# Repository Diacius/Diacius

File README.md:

# Hiya :wave:

I'm a human who occasionally writes code, some of it ends up here.

My pronouns are: he/him

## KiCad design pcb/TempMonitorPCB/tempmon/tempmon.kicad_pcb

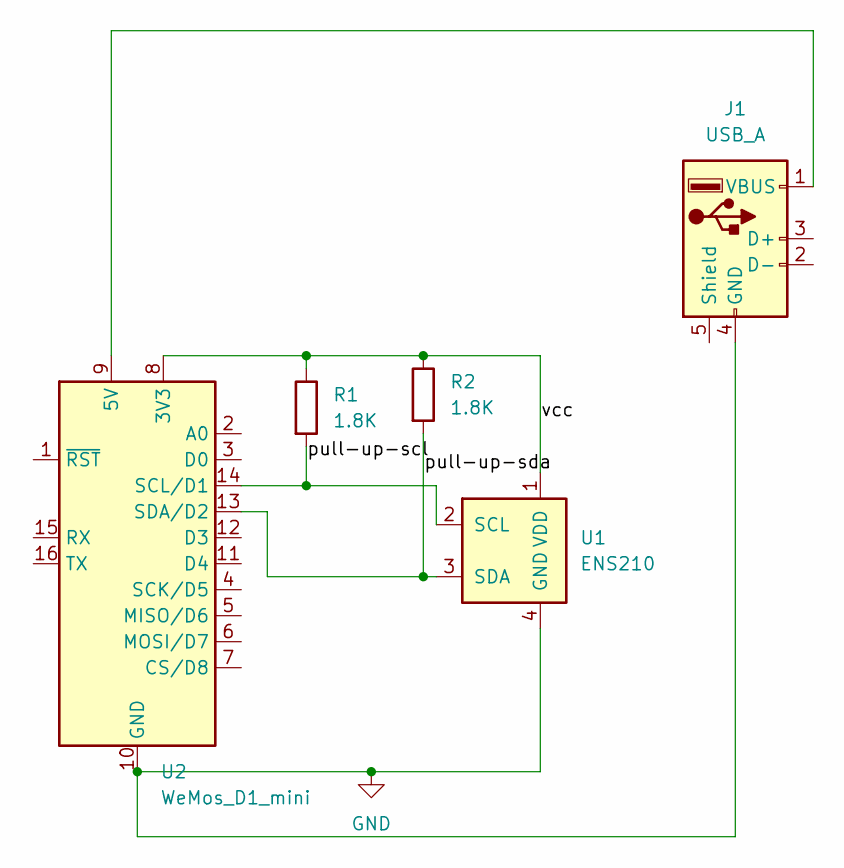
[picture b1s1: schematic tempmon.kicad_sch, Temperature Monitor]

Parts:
J1: USB_A; USB_A_Receptacle_GCT_USB1046
R1, R2: 1.8K; R_Axial_DIN0309_L9.0mm_D3.2mm_P12.70mm_Horizontal
U1: ENS210; AMS_QFN-4-1EP_2x2mm_P0.95mm_EP0.7x1.6mm
U2: WeMos_D1_mini; WEMOS_D1_mini_light

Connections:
/pull-up-scl: R1.2, U1.2 (SCL), U2.14 (SCL/D1)
/pull-up-sda: R2.2, U1.3 (SDA), U2.13 (SDA/D2)
/vcc: R1.1, R2.1, U1.1 (VDD), U2.8 (3V3)
GND: J1.4 (GND), U1.4 (GND), U1.5 (GND), U2.10 (GND)
unnamed: J1.1 (VBUS), U2.9 (5V)

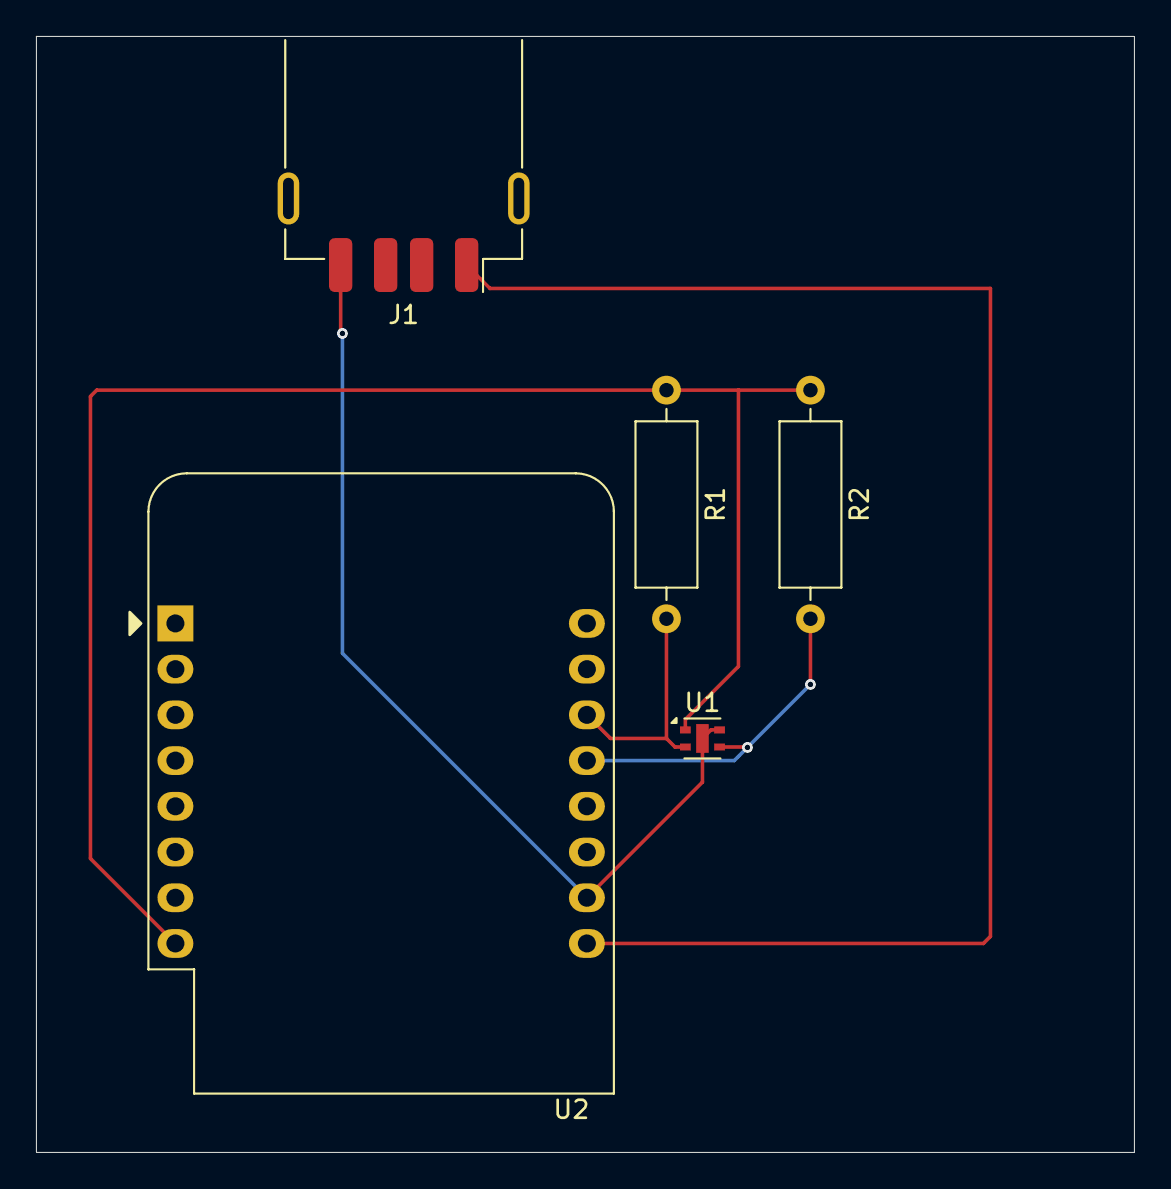
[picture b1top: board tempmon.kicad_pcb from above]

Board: 2 copper layers, 61.0 x 62.0 mm, 5 parts (0 on the bottom side), 5 nets.

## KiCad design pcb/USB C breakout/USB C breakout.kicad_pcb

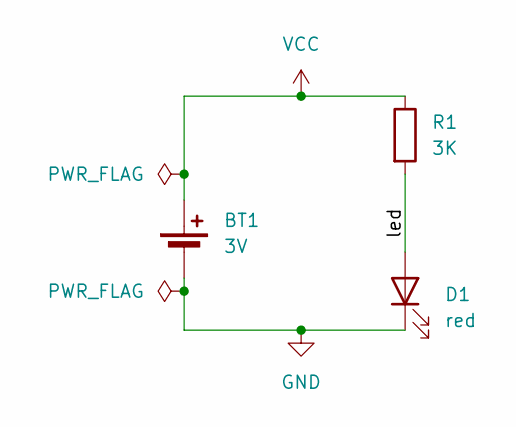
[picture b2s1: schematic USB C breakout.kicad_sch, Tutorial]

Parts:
BT1: 3V; BatteryHolder_Keystone_1058_1x2032
D1: red; LED_D5.0mm
R1: 3K; R_Axial_DIN0309_L9.0mm_D3.2mm_P12.70mm_Horizontal

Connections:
/led: D1.2 (A), R1.2
GND: BT1.2 (-), D1.1 (K)
VCC: BT1.1 (+), R1.1

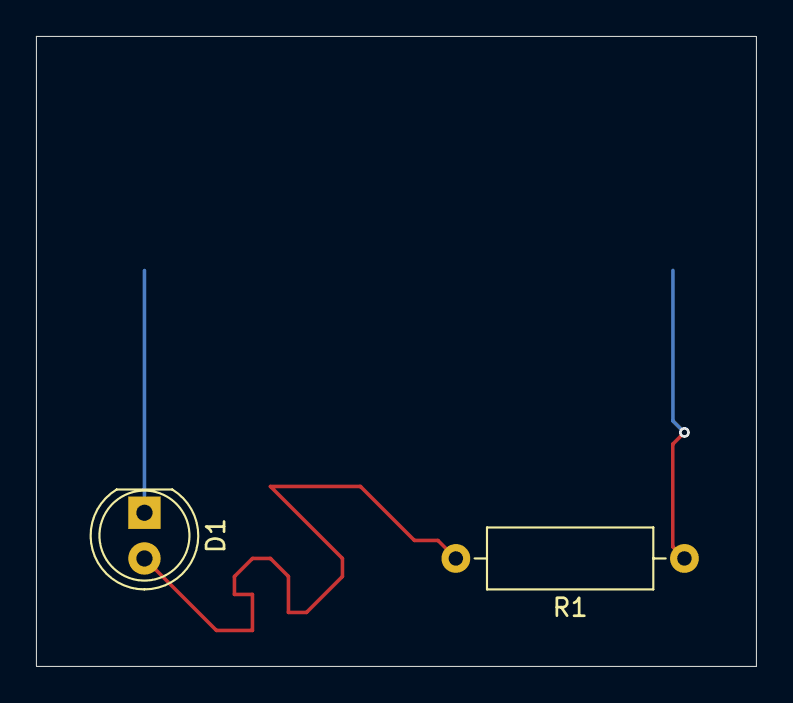
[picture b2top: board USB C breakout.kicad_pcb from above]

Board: 2 copper layers, 40.0 x 35.0 mm, 3 parts (1 on the bottom side), 3 nets.

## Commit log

2021-05-13 remove metrics until I can get them to fully work
2021-05-13 Update github-metrics.svg - [Skip GitHub Action]
2021-05-13 Fix using the wrong user for matrics :facepalm:
2023-05-29 add media family tree
2023-08-14 Create test
2024-06-19 Learning KiCAD
2024-06-19 Starting Work on PCB, needs routing
2024-06-19 Routing Complete :)
    I hope it is at least, I barely know how to make PCBs
2024-06-19 final PCB commit
    not on hakkuun
2024-07-13 Adding Divided Storage
